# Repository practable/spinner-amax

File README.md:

# spinner-amax

Spinner experiment with Maxxon AMAX 32 motor, upgraded for 2022 usage by Controls and Instrumentation 3, School of Engineering, University of Edinburgh. This design has now been used for over 2,500 hours in total across 12 separate instances. We have now expanded the fleet to 48 experiments, with 12 different weights (four of each).

You can cite the contents of this repo via this paper:

D.Reid, J. Burridge, D. Lowe, T. Drysdale "Open-source remote laboratory experiments for controls engineering education," _International Journal of Mechanical Engineering Education_, February 2022, [doi:10.1177/03064190221081451](https://journals.sagepub.com/doi/full/10.1177/03064190221081451)

<figure>

<figcaption align = "center"><b>Fig. 1. Spinner hardware using AMAX motor</b></figcaption>
</figure>

## Contents

  - Firmware `./fw`
  - Hardware `./hw`
  - Printed Circuit Board `./hw/pcb`
  - Single Board Computer `./sbc`
  - UI `./ui`
   
## Hardware

For drawings/CAD files, please look [here](./hw/cad):

[dimensioned drawing of a weight](./hw/cad/weight-drawing.pdf)

[STEP file for the spinner experiment](./hw/cad/spinner.step)

<!--- 
<figure>

<figcaption align = "center"><b>Fig. 2. CAD drawing of the spinner hardware</b></figcaption>
</figure>
--->

### Motor

The experiment is now using an AMAX 32 motor variant (part number: 236668)

The technical specs are [here](./hw/doc/EN-21-176.pdf/)

### Weights

The latest iteration of the weights includes attention to reducing eccentricity to reduce side load on the motor bearings.

### Previous hardware version

The first version of the hardware used a motor with siginficantly more friction, which is educationally useful although increases the challenge level for students just learning the control theory for the first time because the variability induced by the friction can obscure the presence/absence of steady state errors arising from control theory considerations. First version hardware details:  [spinner-nidec](https://github.com/practable/spinner-nidec).

## Performance

The varaibility of the step response is reduced significantly compared to the spinner using the nidec motor.
Meanwhile, here is a measured step response (average of seven runs)

## PCB

## SBC

The scripts to setup your single board computer (in this case, a Raspberry Pi 4 Model B). See the [SBC README](./sbc/README.md) for instructions.

### Token refresh

Refreshing the tokens after installation is a manual process, because shell-relay currently cannot handle ansible connections.

#### Procedure

Use the configure script in `spinner-amax/sbc/scripts` to generate new tokens

```
./configure spin 30 41 https://relay-access.practable.io https://shell-access.practable.io https://shell-access2.practable.io
```

ssh into the spinners one by one (either using the shell-relay connection, or directly). If the shell tokens have expired, then a direct connection is the only option.

```
sudo su
cd /etc/practable
cat data.access #check which experiment 
rm *.token
nano data.token #copy in the token from file in ../autogenerated
nano video.token #copy in token from the file in ../autogenerated
systemctl restart session-rules
cd /usr/local/bin
mv shell shell-relay
cd /etc/systemd/system
systemctl disable shellhost #let's not use the old version any more
nano shellhost2.service #copy in file from ../autogenerated
systemctl enable shellhost2.service
systemctl start shellhost2.service
```

then check the connections to the servers

```
# in admin-tools on admin machine
./sessionrelay/getSessionStats.sh | grep spin
./shellrelay/getShellStats2.sh | grep spin
```

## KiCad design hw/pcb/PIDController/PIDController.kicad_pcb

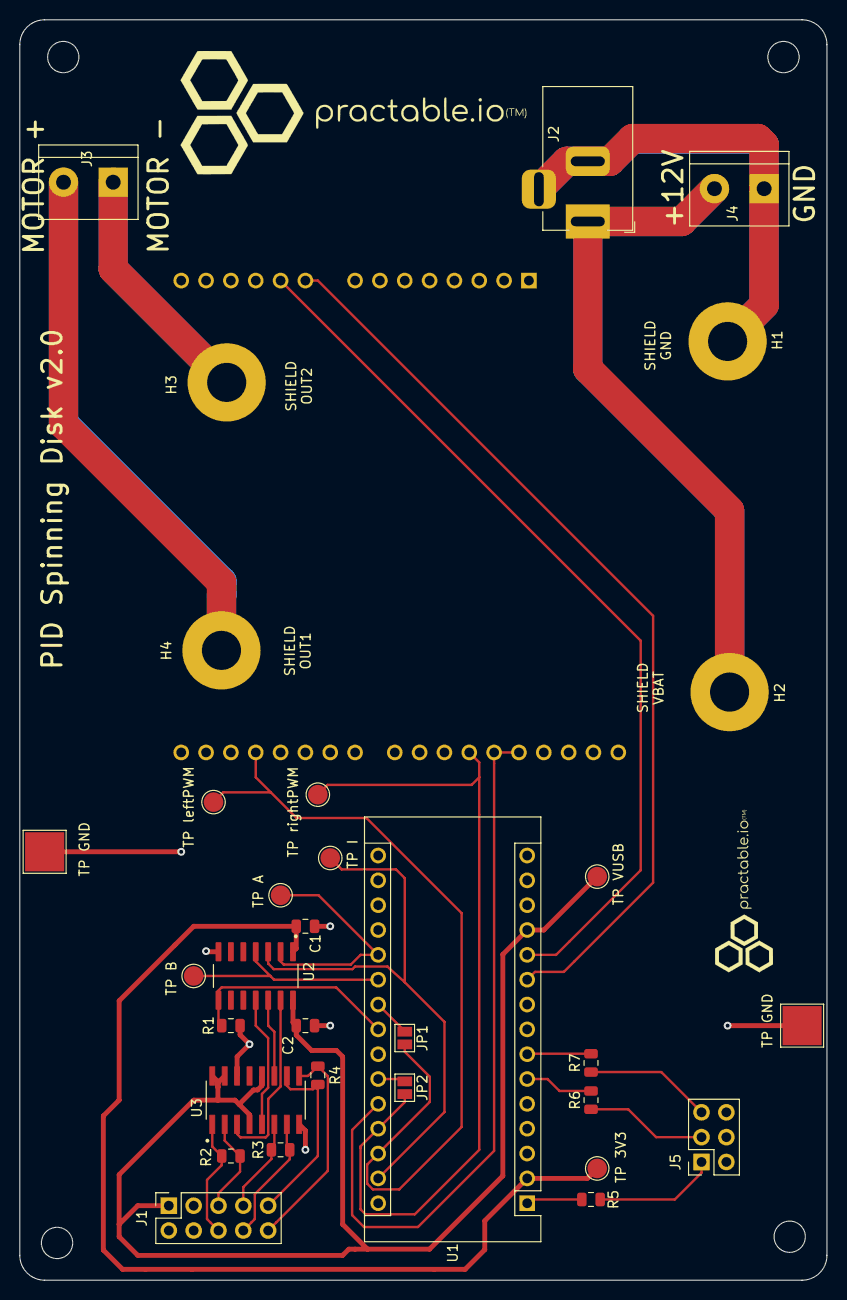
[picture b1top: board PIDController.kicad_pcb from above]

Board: 2 copper layers, 82.6 x 128.9 mm, 33 parts (1 on the bottom side), 34 nets.

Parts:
A1: Arduino_UNO_R3
C1, C2: 0.1uF; C_0805_2012Metric
H1, H2, H3, H4: MountingHole_Pad; MountingHole_4mm_Pad
J1: Conn_02x05_Odd_Even; PinSocket_2x05_P2.54mm_Vertical
J2: Barrel_Jack_Switch; BarrelJack_Horizontal_DC10B
J3, J4: Screw_Terminal_01x02; TerminalBlock_bornier-2_P5.08mm
J5: Conn_02x03_Odd_Even; PinSocket_2x03_P2.54mm_Vertical
JP1, JP2: SolderJumper_2_Open; SolderJumper-2_P1.3mm_Open_Pad1.0x1.5mm
R1: 5k; R_0805_2012Metric
R2, R3, R4: 2k; R_0805_2012Metric
R5, R6, R7: 200; R_0805_2012Metric
TP 3V3: TestPoint; TestPoint_Pad_D2.0mm
TP A: TestPoint; TestPoint_Pad_D2.0mm
TP B: TestPoint; TestPoint_Pad_D2.0mm
TP GND: TestPoint; TestPoint_Pad_4.0x4.0mm
TP GND#2: TestPoint; TestPoint_Pad_4.0x4.0mm
TP I: TestPoint; TestPoint_Pad_D2.0mm
TP VUSB: TestPoint; TestPoint_Pad_D2.0mm
TP leftPWM: TestPoint; TestPoint_Pad_D2.0mm
TP rightPWM: TestPoint; TestPoint_Pad_D2.0mm
U1: Arduino_Nano_33_IoT; Arduino_Nano
U2: TXS0104ED; SOIC127P600X175-14N
U3: SN75175D; SOIC127P600X175-16N

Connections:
3V3: C1.2, TP 3V3.1, U1.2, U2.1
A: U2.13, U3.3
B: U2.11, U3.5
CURRENT_1: A1.9, U1.10
CURRENT_2: A1.10, U1.11
ENABLE: A1.27, A1.28, U1.26
ENCODER_A: J1.5, R2.1, U3.2
ENCODER_B: J1.7, R3.1, U3.6
ENCODER_INDEX: J1.9, R4.1, U3.10
ENCODER_NOT_A: J1.6, R2.2, U3.1
ENCODER_NOT_B: J1.8, R3.2, U3.7
ENCODER_NOT_INDEX: J1.10, R4.2, U3.9
GND: A1.6, A1.7, A1.29, C1.1, C2.1, J1.4, J5.2, J5.4, J5.6, R1.2, TP GND.1, TP GND#2.1, U1.14, U1.19, U2.7, U3.8, U3.14
I: U2.12, U3.11
LED1: R5.2, U1.1
LED2: R6.2, U1.6
LED3: R7.2, U1.7
unnamed: H1.1, J2.2, J2.3, J4.1
unnamed: H2.1, J2.1, J4.2
unnamed: H3.1, J3.1
unnamed: H4.1, J3.2
unnamed: J5.1, R5.1
unnamed: J5.3, R6.1
unnamed: J5.5, R7.1
unnamed: JP1.1, U1.22
unnamed: JP2.1, U1.25
unnamed: U1.13, U1.18
OE: R1.1, U1.23, U2.8
PIN_A: TP A.1, U1.20, U2.2
PIN_B: TP B.1, U1.21, U2.4
PIN_INDEX: TP I.1, U1.29, U2.3
VUSB: C2.2, J1.1, TP VUSB.1, U1.12, U2.14, U3.4, U3.12, U3.15, U3.16
leftPWM: A1.18, JP1.2, TP leftPWM.1, U1.28
rightPWM: A1.26, JP2.2, TP rightPWM.1, U1.27

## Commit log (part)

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2021-11-16 Add status to README.md
2021-11-16 Add motor info to README.md
2021-11-16 Fix image path in README.md
2021-11-16 Add part number to README.md
2021-11-18 additional hardware docs added
2022-04-26 Feat (fw): add firmware
    The firmware comes from dpreid/pidcontroller/SpinningDiskController,
    with some tidying up to remove files associated with the other
    experiments that repo was covering. This version of the firmware was
    used to deliver >2,500 hours of experimental usage in 2022.
2022-04-26 Doc (README.md): update description
2022-04-26 Feat (fw): Add Filter library
2022-04-26 fix (fw): Move filter test to ./test
2022-04-26 Fix (fw): mv filter lib files
    Arduino can't find header files more than one level deep in the library
    directory, it seems, so re-factor the fw/libraries/Filter library and
    test to work with arduino_cli and gtest by moving filter.h up a level
    and fixing CMakeLists.txt for the test to reflec that.
2022-04-26 fix (fw/Filter): fix NilFilter test
2022-04-26 feat (fw): add test/filter-python
2022-04-26 feat (fw/test/filter-python): add hello
2022-04-27 pcb and ui files added
2022-04-27 removed superfluous hardware doc
2022-04-28 test (fw): update filter_test
2022-08-25 Add sbc
2022-08-30 changes to pid parameters on change event
2022-08-30 updated gitignore
2022-08-31 limited voltage to 6V
2022-09-06 Remove password from sbc/README
2023-01-11 sbc (fix): change secret filenames in scripts
2023-01-11 README (docs): add manual token refresh procedure
2023-02-21 ui (fix): vite migration wip
2023-02-21 ui (fix): build works but no display
2023-02-21 index.html (fix): copy in known good version
2023-02-21 ui (fix): icon link
2023-02-21 ui (fix): jsmpeg dep fixed
2023-02-21 VideoElement.vue (fix): revert to original JSMpeg import name
2023-02-22 ui (fix): update from dpreid fork
    timdrysdale moved the ui to vite for use with the new system, so this
    commit is combining the vite build files from that effort with the
    latest source from dpreid's forked version of the repo. Migrating this
    ui involved updating and re-patching our fork of the jsmpeg-player dependency to
    avoid a node gyp error on trying to install it.
2023-02-24 ui (fix): chart.js version
2023-03-02 sbc (fix): pin relay v0.2.3
2023-03-08 README (fix): add citation details
2023-03-08 README (fix): fix hw link
2023-03-08 README (fix): fix citation link
2023-03-08 README (fix): add weight drawing and spinner step
2023-03-08 README (fix): update spinner.step
2023-04-25 updated to vitest but need to fix mock of websocket
2023-04-25 changed file path format in navigation bar
2023-04-25 updated layout of pid parameter inputs and set a min width
2023-04-25 fixed issue with attempting to update pid params when hardware is running
2023-04-25 updated image paths
2023-04-25 updated more image paths
2023-04-26 data stops recording when a limit is reached. Also resets the step and ramp input to false
2023-04-26 fixed wrong colour at end of plotted line
2023-04-26 increased max plotting data points to 2000
2023-04-26 added data point count on graph component
2023-04-26 separated into analytics and default
2023-04-26 updated consent to check after course is set via a watcher
2023-04-26 default and analytics folders now ready
2024-04-22 ui (fix): vitest config added and package version update to 3.0.0
2024-04-22 ui (fix): added dark theme toggle and update of CSS style, not all components yet though
2024-04-22 css (update): major css components updated
2024-04-22 ui (fix): popup help changed to modal
2024-04-22 ui (fix): container-sm changed to container-fluid for responsiveness
2024-04-22 ControlPanelSpinningDisk (update): css styling updated
2024-04-22 ControlPanel (updated): css on this component updated
2024-04-23 DataRecorder (fix): set index added to datasets
2024-04-23 TableOutput (fix): update to plot datasets separately
2024-04-23 GraphOutput (fix): plots datasets in different colours and includes labels for show/hide datasets
2024-04-23 ui (update): drag functionality updated
2024-04-23 App (update): userName now used for UUID
2024-04-23 ui (fix): logging and achievements removed - stores still exist for now until decide how to add them back in
2024-04-23 ui (fix): loading data on start updates the dataset index appropriately
2024-04-23 ui (fix): popups updated to modals
2024-04-23 ui (fix): popuphelp closes on lose focus (blur)
2024-04-23 ui (fix): achievement store removed
2024-04-23 ui (fix): removed any reference to variable governor and robot arm labs
2024-04-23 ui (fix): ramp command updated to reflect changes to step command
2024-04-23 ui (fix): accessibility issues fixed, still need to check colour contrast for warning buttons and text in navigation bar
2024-04-25 ui (fix): run/stop button stays in same position now and input type remains on screen but disabled whilst mode running
2024-04-25 ui (fix): enabled config file reading, particularly for lab ID in naviagation bar
2024-04-25 ui (fix): simplified consent to one consent for practable in general asks if consent is false on startup
2024-04-25 ui (fix): graph labels now show corresponding colour of dataset
2024-04-25 ui (fix): consent dialog updated
2024-04-25 ui (fix): responsive design for mobile updated
2024-04-25 ui (fix): added aria-labels where necessary for accessibility
2024-04-29 ui (fix): update build path to spinner-default-3.0
2024-06-14 created new analytics UI using new Logging.vue component and config
2024-06-14 GraphOutput (fix): add ids to select options
2024-06-14 testing logging and removed analytics to update default first
2024-06-14 default (ui): old logging components removed from components, but files remain for now. Logic for consent remains until decision on whether consent required
2024-06-14 analytics (ui): add latest components with analytics for identifying missing ids
2024-06-14 ids added to components that were missing them
2024-06-14 analytics (ui): changes to default pushed to analytics too
2024-06-14 Logging added back into analytics UI
2024-06-17 Logging (fix): remove console logs
2024-06-18 StepCommand, RampCommand (update): ids on buttons for sending hardware commands updated to differentiate them
2024-06-18 minor update to logging config to correct error in button ids in graph node object
2024-06-20 Logging updated so that other means of sending a voltage step also register graph edges
2024-06-27 DOM (feat): update id for main interactive components to provide meaningful names for logging
2024-06-27 ShowHardwareConfigButton (feat): add component for displaying spinner disk dimensions
2024-06-28 default css colour scheme decided in theme-new
2024-06-28 css theme set (for now)
2024-06-28 layout updates in CSS - need to update component templates
2024-06-28 GraphOutput (feat): update graph component to fit new layout
2024-07-01 GraphOutput now completely resizable and fills div element
2024-07-01 GraphOutput (fix): colour of grid lines and ticks
2024-07-01 GraphOutput (fix): minor change to spacing between toolbar and graph
2024-07-02 smoothie vuex updated but not working yet
2024-07-03 smoothie chart update, need to update options toolbar
2024-07-04 WebcamStream (fix): moved toolbar out of video element and into webcamstream to combine with options for smoothie
2024-07-04 WebcamStream (fix): smoothie options updated and working
2024-07-04 Toolbar (delete): removed Toolbar component, so now individual components are added separately to make up a toolbar
2024-07-04 WebcamStream (feat): smoothie options has a reset button
2024-07-04 ControlPanel (feat): update ControlPanel component
2024-07-04 NavigationBar (fix): minor update to positions and removed layout options
2024-07-04 ControlPanel (fix): changed spacing for large screens only
2024-07-05 GraphOutput (fix): gradient calculation updated and tested
2024-07-05 ControlPanel (feat): responsive design flex features added
2024-07-08 Stopwatch and SystemDiagrams removed
2024-07-08 updated layout to better fit table and snapshot components
2024-07-08 PopupHelp added to all relevant components and content updated
2024-07-08 tooltips added to all button-toolbar components
2024-07-08 removed scroll into view behaviour on add component as was not what was expected
2024-07-08 adding modals to body and removing again
2024-07-08 OptionsTool and PopupHelp updated to use nextTick to attach and remove modal from body to ensure correct display
2024-07-08 ControlPanel and GraphOutput updated toolbar stickiness for appropriate behaviour
2024-07-09 vertical resize of rows added
2024-07-09 GraphOutput (fix): function plotting modal layout
2024-07-09 overflow-x set to hidden as there should be no horizontal scrolling of the app window and this hides the resize button at the bottom
2024-07-09 GraphOutput (fix): updated updateChart function so that correct behaviour seen on toggle theme when max data already reached
2024-07-09 GraphOutput (fix): update of scatter chart y axis moved to a watcher function on getGraphDataParameter instead of updating on each graph update cycle
2024-07-09 GraphOutput (fix): graph-canvas is now contains a ref to access it in the DOM instead of getElementByID
2024-07-11 analytics ui changed to include new updates in default
2024-09-17 analytics-v3 (update): added basic authorization to logging
2024-09-17 logging.js (updated): remove old logic for websocket connection to logging server
2024-09-18 removed old logging components from default and added new in. Added requirement for consent to activate logging in default and analytics
2024-09-18 logging consent updated and added experiment code to logs
2024-09-18 default ui (update): update logging store to match analytics
2024-09-30 added check marks to component dropdown in nav bar
2024-09-30 minor styling changes on table and snapshot
2024-10-01 App (fix): update css style update on drag event for non-firefox browsers
2024-10-01 setDraggable (fix): add onmouseleave event to set setDraggable back to true. Without this it was possible for draggable elements to leave the UI setDraggable to false if the mouse moved out of the el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
2024-10-01 add setDraggable(true) for mouseleave event in DEFAULT UI this time
2024-11-19 ui (update): minor update to button css
2025-01-09 analytics ui (fix): updated to sync with default ui
2025-01-09 GraphOutput (feat): have added a custom event to tooltips so that logging can capture hovering over data points in the chartjs canvas
2025-01-10 GraphOutput (update): add try catch to chartdatahover event dispatch to cover any possible tooltip popup
2025-01-10 NavigationBar (feat): add UUID display back into navigation bar and remove consent settings from nav bar
2025-01-10 App (fix): remove consent modal and fix consent to true in analytics version of UI
2025-01-10 analytics UI (fix): .env.production updated to reflect location for this UI
2025-01-13 ui env files (fix): updated for build to ed0
2025-06-05 ui/analytics (update): logging update to now include log version and session-expired key
2025-06-09 ui/analytics (update): minor change, removing spaces in method, no change to functionality
2025-09-02 ui/default (fix): add version to information popup
2025-09-02 ui/analytics (fix): version in logging is now connected to the app version
2025-09-02 ui/analytics (fix): add version to information popup
2025-09-02 ui/README.md (add): readme with UI variant and latest version details
